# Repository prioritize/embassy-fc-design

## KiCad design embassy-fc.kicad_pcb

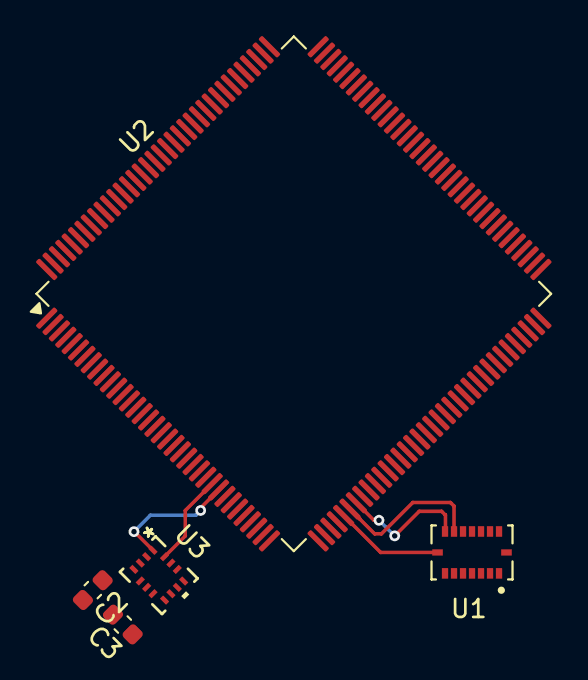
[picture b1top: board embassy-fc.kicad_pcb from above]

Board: 2 copper layers, 5 parts (0 on the bottom side), 11 nets.

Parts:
C2, C3: 100nF; C_0603_1608Metric
U1: BMI088
U2: STM32H753ZITx; LQFP-144_20x20mm_P0.5mm
U3: BMI270; BMI270_BOS

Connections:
GND: C2.2, U1.2 (NC), U1.4 (GNDA), U1.6 (GNDIO), U1.7 (PS), U3.7 (GND)
unnamed: U2.16 (VSS), U2.38 (VSS), U2.51 (VSS), U2.61 (VSS), U2.83 (VSS), U2.94 (VSS), U2.107 (VSS), U2.120 (VSS), U2.130 (VSS)
unnamed: C3.2, U3.6 (GNDIO)
SP1_SCK: U1.8 (SCL/SCK), U2.41 (PA5)
SPI1_MISO: U1.10 (SDO2), U1.15 (SDO1), U2.42 (PA6)
SPI1_MOSI: U1.9 (SDA/SDI), U2.43 (PA7)
SPI2_MISO: U2.28 (PC2_C), U3.1 (SDO)
SPI2_MOSI: U2.27 (PC1), U3.14 (SDX)
SPI2_SCK: U2.69 (PB10), U3.13 (SCX)
VDD: C2.1, U1.3 (VDD), U3.5 (VDDIO)
VDDIO: C3.1, U1.11 (VDDIO), U3.8 (VDD)

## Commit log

2025-05-13 removing files from gitignore
2025-05-15 progress
